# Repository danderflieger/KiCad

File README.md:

# KiCad
This repository contains all of my electronics designs made in KiCad. KiCad is an open source software that allows you to design electronics schematics and PCB layouts.

For PCB etching, I print the PCB files on glossy paper using a laser printer. Depending on the board, they might be printed mirrored or not. Pay close attention to what pins go where before etching.

Once I have the PCB layout printed, I place the paper on a single sided, copper clad PCB blank and tape it in place with masking tape. Then I use an iron on a high setting (usually cotton or higher) and iron the board side (e.g. paper down on a flat surface) for a few minutes. Then I place the entire thing (paper and board) under cold water for several minutes until the water seeps through the paper enough to break down and peel away.

Then I use an Exacto knife to remove any toner that bled to where I dont want it (sometimes the iron squeezes it and traces are too close together). And I use a fine-tipped permanent marker to repair any areas where the toner peeled off with the paper.

Once Im happy with how everything looks, I make a mixture of 2 parts white vinegar (5% acidity), 1 part Hydrogen Peroxide (%3) and a dash of NON-IODIZED salt. I stir the chemicals until the salt dissolves.

Then I drop the cooper clad board into the mixture and agitate it for 15-20 minutes until the unwanted copper is gone. The chemicals will turn a light blue/turquoise color as they dissolve the copper. 

A good way to tell if the etching is complete is to pull it out of the etchant and hold it up to a light. You will be able to see the traces through the back side of the board.

Rinse off the etchant and then use acetone to remove the toner. As you do, you will see copper traces where the toner used to be.

Next, drill any through holes with a 0.1mm drill bit. I have to use a drill press because my hands aren't steady enough and I end up breaking drill bits.

Finally, place the electronics through the holes from the back side and solder the pins on the side with copper traces.

Because copper will continue to oxidize, you may want to consider using some clear fingernail polish over the traces to protect them from the open air.

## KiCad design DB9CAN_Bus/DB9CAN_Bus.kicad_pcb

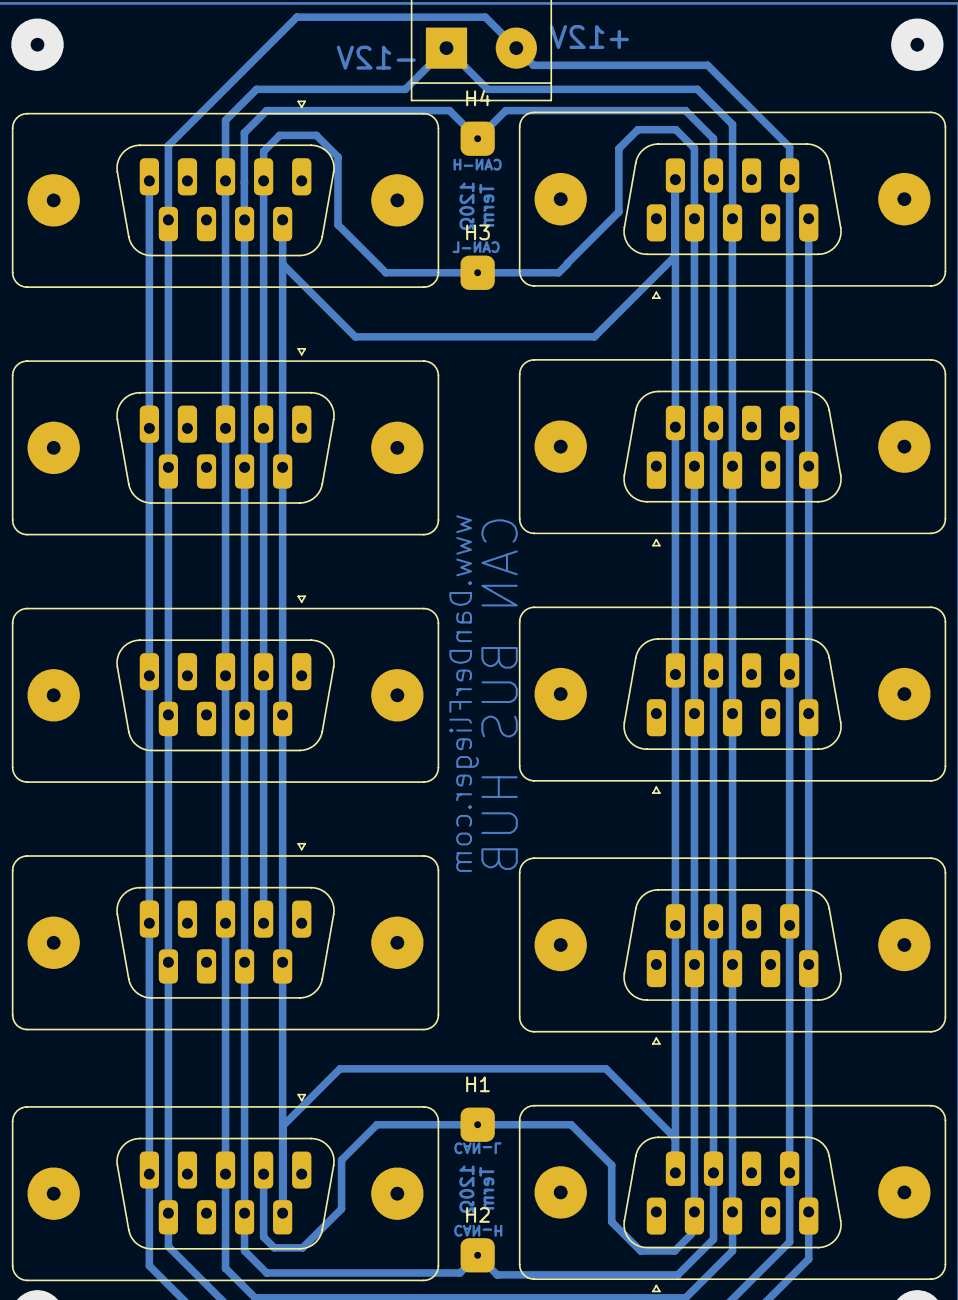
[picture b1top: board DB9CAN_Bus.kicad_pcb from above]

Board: 2 copper layers, 15 parts (0 on the bottom side), 6 nets.

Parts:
H1, H2, H3, H4: MountingHole_Pad; MountingHole_2.2mm_M2_DIN965_Pad
J1, J2, J3, J4, J5, J6, J7, J8, J9, J10: DE9_Receptacle; DSUB-9_Female_Vertical_P2.77x2.84mm_MountingHoles Custom Pa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
J11: Screw_Terminal_01x02; TerminalBlock_bornier-2_P5.08mm

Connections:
unnamed: H1.3 (1), H3.2 (1), J1.2, J2.2, J3.2, J4.2, J5.2, J6.2, J7.2, J8.2, J9.2, J10.2
unnamed: H2.4 (1), H4.1, J1.7, J2.7, J3.7, J4.7, J5.7, J6.7, J7.7, J8.7, J9.7, J10.7
unnamed: J1.5, J2.5, J3.5, J4.5, J5.5, J6.5, J7.5, J8.5, J9.5, J10.5
unnamed: J1.6, J2.6, J3.6, J4.6, J5.6, J6.6, J7.6, J8.6, J9.6, J10.6
unnamed: J1.3, J2.3, J3.3, J4.3, J5.3, J6.3, J7.3, J8.3, J9.3, J10.3, J11.1
unnamed: J1.9, J2.9, J3.9, J4.9, J5.9, J6.9, J7.9, J8.9, J9.9, J10.9, J11.2

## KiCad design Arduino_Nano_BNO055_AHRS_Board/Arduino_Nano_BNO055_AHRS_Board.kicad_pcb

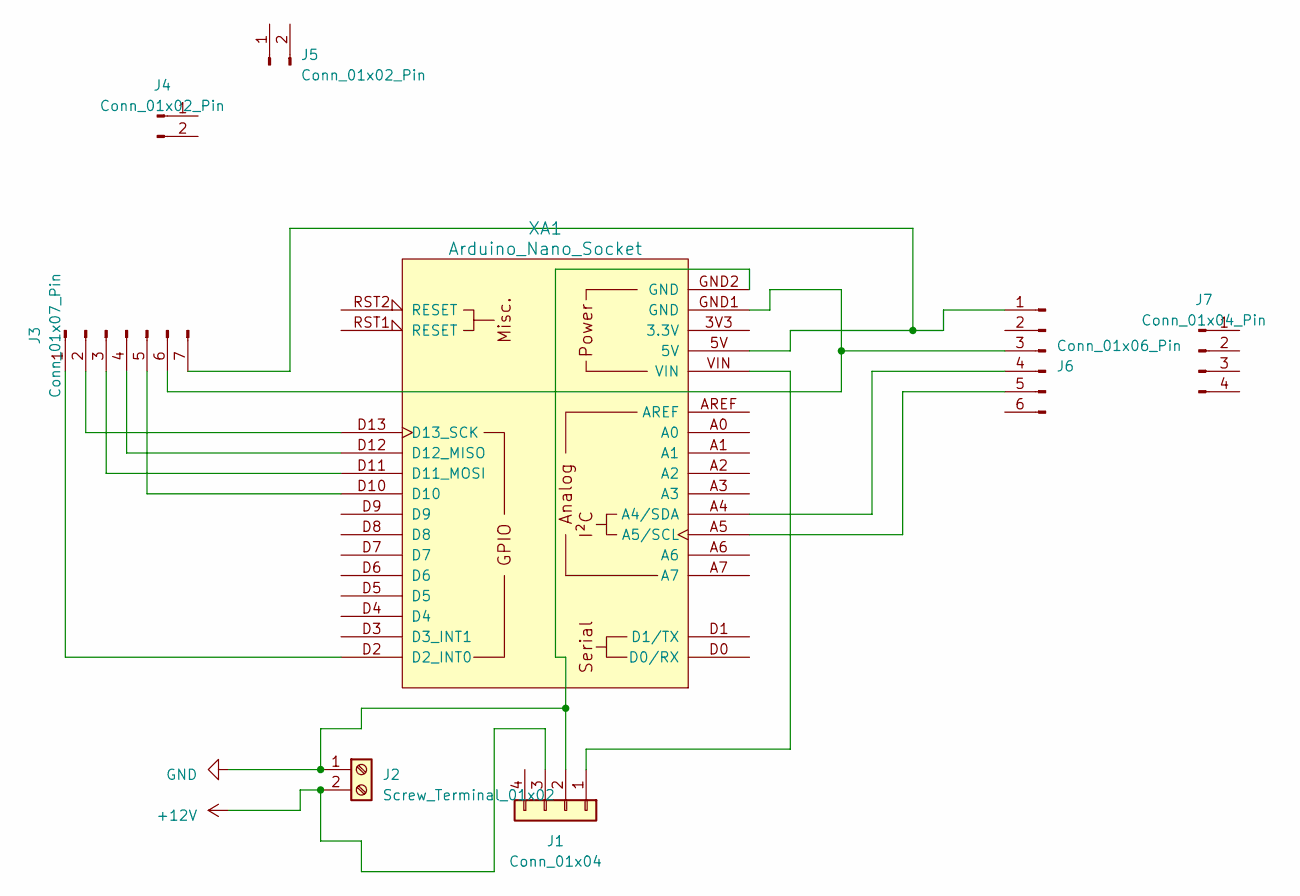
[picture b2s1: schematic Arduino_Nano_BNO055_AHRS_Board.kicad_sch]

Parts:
J1: Conn_01x04; PinSocket_1x04_P2.54mm_Vertical
J2: Screw_Terminal_01x02; TerminalBlock_bornier-2_P5.08mm
J3: Conn_01x07_Pin; PinHeader_1x07_P2.54mm_Vertical
J4, J5: Conn_01x02_Pin; PinHeader_1x02_P2.54mm_Vertical
J6: Conn_01x06_Pin; PinHeader_1x06_P2.54mm_Vertical
J7: Conn_01x04_Pin; PinHeader_1x04_P2.54mm_Vertical
XA1: Arduino_Nano_Socket

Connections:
+12V: J1.3, J2.2
GND: J1.2, J2.1, XA1.GND2 (GND)
unnamed: J1.1, XA1.VIN
unnamed: J3.1, XA1.D2 (D2_INT0)
unnamed: J3.2, XA1.D13 (D13_SCK)
unnamed: J3.3, XA1.D11 (D11_MOSI)
unnamed: J3.4, XA1.D12 (D12_MISO)
unnamed: J3.5, XA1.D10
unnamed: J3.6, J6.3, XA1.GND1 (GND)
unnamed: J3.7, J6.1, XA1.5V
unnamed: J6.4, XA1.A4 (A4/SDA)
unnamed: J6.5, XA1.A5 (A5/SCL)

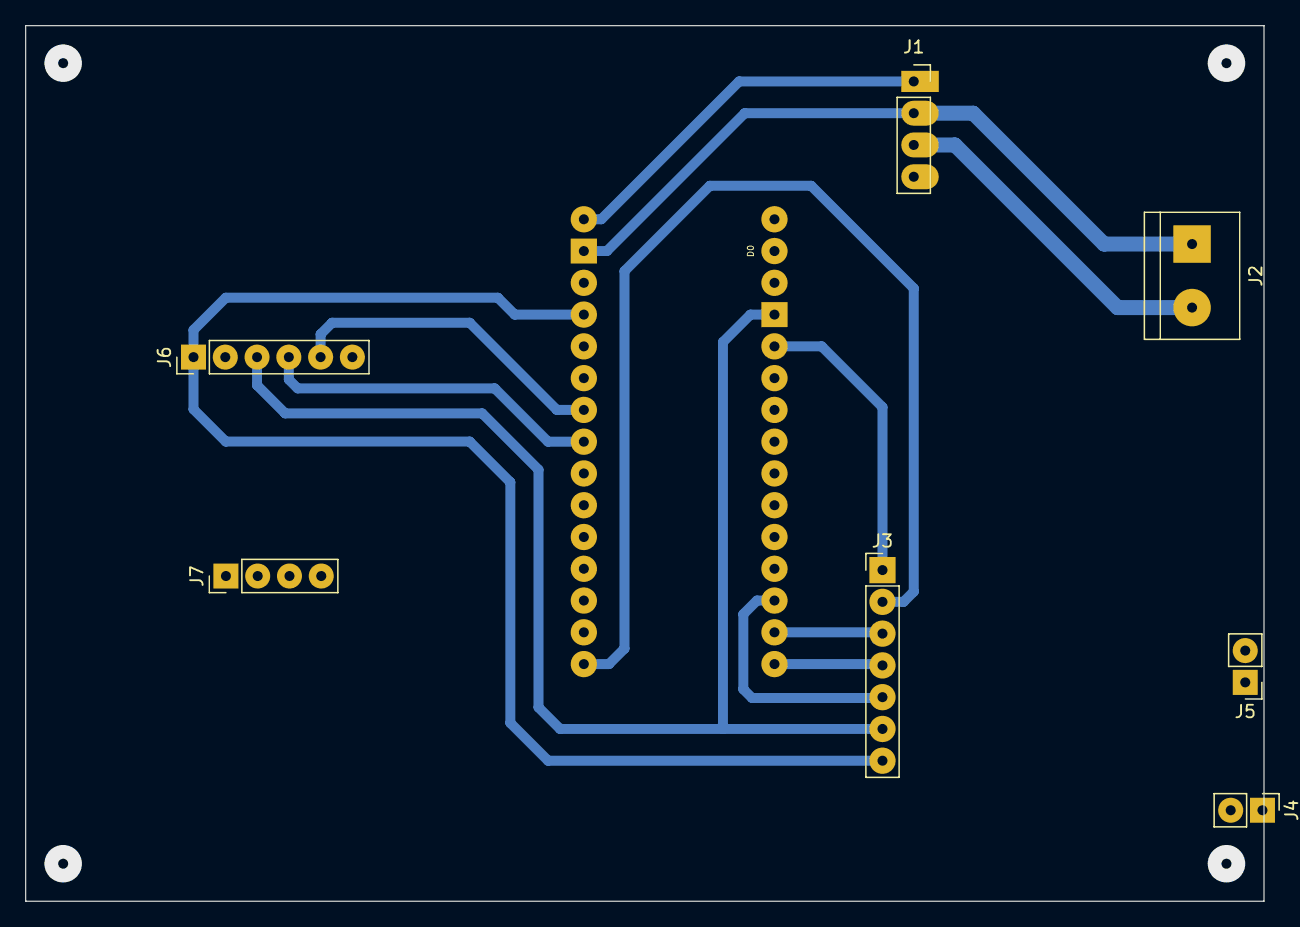
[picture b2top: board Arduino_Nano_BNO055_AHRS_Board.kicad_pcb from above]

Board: 2 copper layers, 99.0 x 70.0 mm, 8 parts (1 on the bottom side), 12 nets.

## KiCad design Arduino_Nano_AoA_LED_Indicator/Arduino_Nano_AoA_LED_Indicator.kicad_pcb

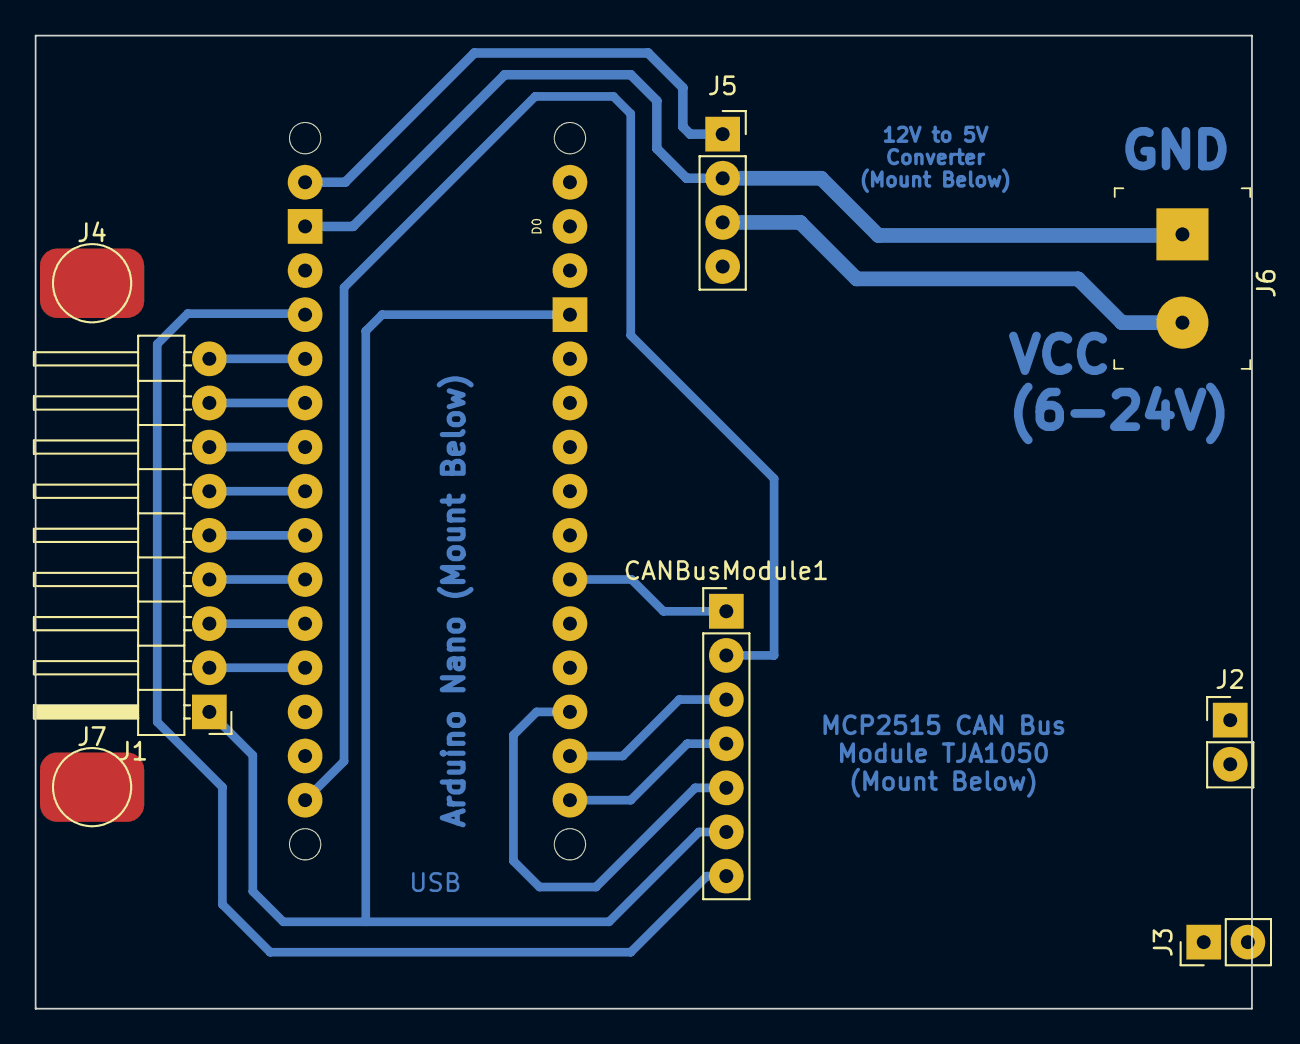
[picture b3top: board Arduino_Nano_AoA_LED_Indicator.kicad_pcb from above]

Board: 2 copper layers, 70.0 x 56.0 mm, 9 parts (1 on the bottom side), 18 nets.

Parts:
A1: Arduino_Nano_Socket
CANBusModule1: MCP2515; PinHeader_1x07_P2.54mm_Vertical
J1: Conn_01x09_Pin; PinHeader_1x09_P2.54mm_Horizontal
J2, J3: Conn_01x02_Pin; PinHeader_1x02_P2.54mm_Vertical
J4: SolderPad1; TestPoint_Pad_D4.0mm
J5: Conn_01x04; PinSocket_1x04_P2.54mm_Vertical
J6: OSTTC022162; Term_Block_1x2_P5.08MM
J7: SolderPad2; TestPoint_Pad_D4.0mm

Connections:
+12V: J5.3, J6.2
GND: A1.GND2 (GND), J5.2, J6.1
unnamed: A1.A4 (A4/SDA), J1.6
unnamed: A1.A5 (A5/SCL), J1.7
unnamed: A1.D11 (D11_MOSI), CANBusModule1.3
unnamed: A1.D12 (D12_MISO), CANBusModule1.4
unnamed: A1.D13 (D13_SCK), CANBusModule1.2
unnamed: A1.D7, CANBusModule1.1
unnamed: A1.D10, CANBusModule1.5
unnamed: A1.GND1 (GND), CANBusModule1.6, J1.1
unnamed: A1.5V, CANBusModule1.7
unnamed: A1.A0, J1.2
unnamed: A1.A1, J1.3
unnamed: A1.A2, J1.4
unnamed: A1.A3, J1.5
unnamed: A1.A6, J1.8
unnamed: A1.A7, J1.9
unnamed: A1.VIN, J5.1

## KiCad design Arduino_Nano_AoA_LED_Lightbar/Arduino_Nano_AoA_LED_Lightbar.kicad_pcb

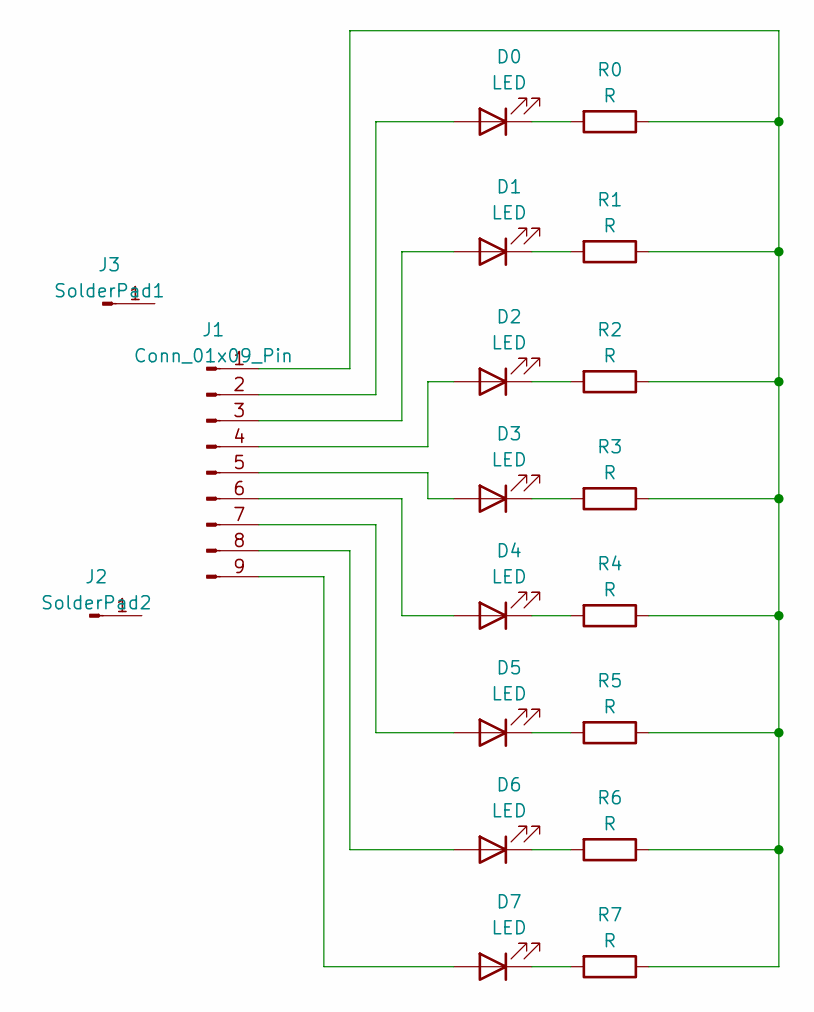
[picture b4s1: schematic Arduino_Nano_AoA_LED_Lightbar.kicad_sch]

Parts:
D0, D1, D2, D3, D4, D5, D6, D7: LED; LED_Yuji_5730
J1: Conn_01x09_Pin; PinHeader_1x09_P2.54mm_Vertical
J2: SolderPad2; TestPoint_Pad_D4.0mm
J3: SolderPad1; TestPoint_Pad_D4.0mm
R0, R1, R2, R3, R4, R5, R6, R7: R; R_1206_3216Metric

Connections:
unnamed: D0.2 (A), J1.2
unnamed: D0.1 (K), R0.2
unnamed: D1.2 (A), J1.3
unnamed: D1.1 (K), R1.2
unnamed: D2.2 (A), J1.4
unnamed: D2.1 (K), R2.2
unnamed: D3.2 (A), J1.5
unnamed: D3.1 (K), R3.2
unnamed: D4.2 (A), J1.6
unnamed: D4.1 (K), R4.2
unnamed: D5.2 (A), J1.7
unnamed: D5.1 (K), R5.2
unnamed: D6.2 (A), J1.8
unnamed: D6.1 (K), R6.2
unnamed: D7.2 (A), J1.9
unnamed: D7.1 (K), R7.2
unnamed: J1.1, R0.1, R1.1, R2.1, R3.1, R4.1, R5.1, R6.1, R7.1

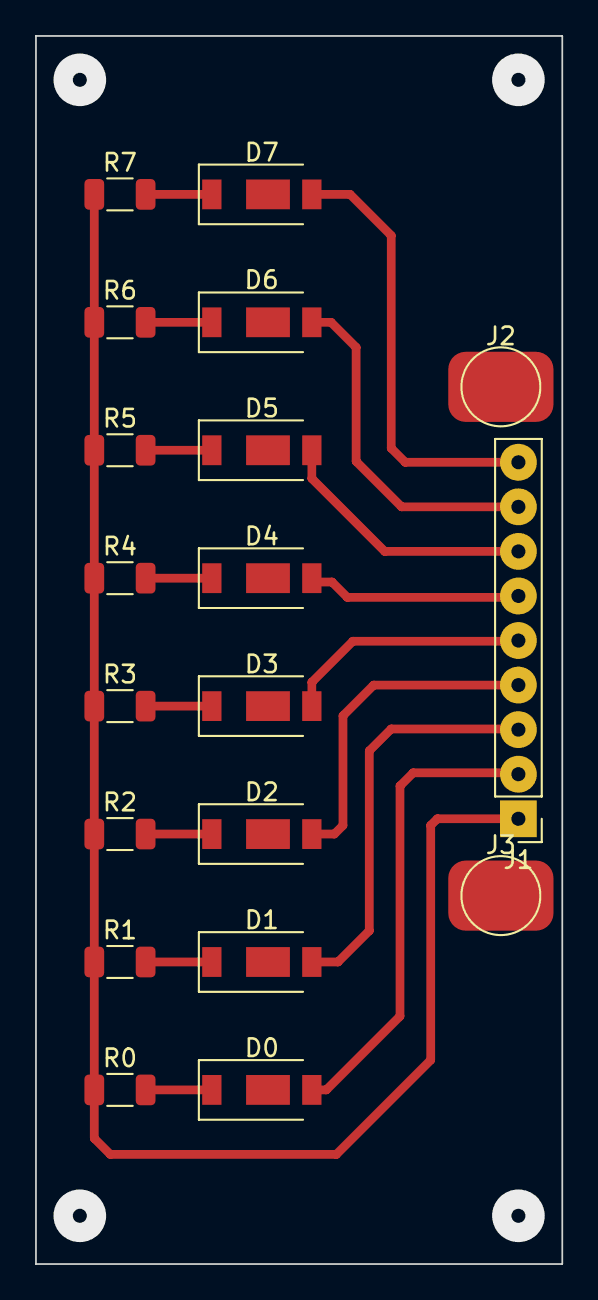
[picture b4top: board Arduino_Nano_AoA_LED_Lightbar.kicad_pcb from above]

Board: 2 copper layers, 30.0 x 70.0 mm, 19 parts (0 on the bottom side), 17 nets.

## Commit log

2023-08-08 Added first commit.
2023-08-10 Added a new PCB design for an AHRS board that uses the Adafruit BNO055 9-axis IMU breakout board. The BNO055 connects to an Arduino Nano (just like the rest of my designs).
2023-08-10 Made one update that I didn't save ...
2023-08-19 Updates Arduino_Nano_BNO055_AHRS_Board files. The older version required a via to cross two traces. This new version uses a larger PCB blank (one-sided) and no longer requires any vias. I also moved 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
2023-08-23 Started a new LED bar project for AoA indication (e.g. several surface mounted LEDs that individually light up as your AoA increases). This will listen for AoA CAN messages from an AoA sensor and ind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
2023-08-24 Split the AOA LED project into two projects - one for the LEDs and one for the Nano board and the MCP2515 CAN board.
2023-10-11 Created a .pdf file of the DB9CAN_Bus PCB file.
2023-10-16 Created a new board for the Wit-Motion WT901B IMU chip.
2025-02-04 Added a PDF file for the ASI/AoA board.
